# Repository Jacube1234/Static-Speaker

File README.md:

# Static-Speaker

<br>
View PCB on KiCanvas

This is my custom radio combined with a speaker designed for the YSWS Static
I chose this project to upgrade the standard kit by integrating an M18 Bluetooth module alongside the original RDA5807 FM radio chip, transforming it into a permanent Bluetooth speaker for my bedroom while keeping the physical over-the-air FM radio chip!

## Features:
- Bluetooth audio streaming directly from a phone
- Over-the-air local FM Radio playback
- One physical push-button to switch modes
- Dual analog potentiometers for volume control

## CAD Model:

## PCB

Schematic

Layout

PCB

## Firmware Overview
Runs on CircuitPython using an RDA5807 library wrapper. A `code.py` script handles I2C tuning for the FM radio, manages the M18 module's mute line via pin A3 (`BT_MUTE`), and toggles between Bluetooth and FM sources using a push button (`SW1`).

## File structure

There's 3 main folders: Firmware, PCB, and Production. The PCB folder contains .kicad_pcb, .kicad_pro, and .kicad_sch. The Firmware folder contains files for the Seeed Xiao code. The production folder will have files for the PCB printing.

## BOM (Bill of Materials):
Here should be everything you need to make this speaker
Most things should be what static sends you except the bluetooth module.

- 1x Seeed Studio XIAO RP2040
- 1x MH-M18 Bluetooth Audio Module
- 1x RDA5807FP FM Radio Tuner Chip
- 1x TDA2822 Audio Amplifier Chip
- 1x WH148 10kΩ Potentiometer
- 4x 1kΩ Resistors 
- 1x 3.5mm Jack (for FM Radio Antenna)
- 2x 10uF Capacitors
- 2x 100uF Capacitors
- 2x 30mm Speakers
- 1x 12mm Momentary Push Button Mode switch
- Hookup wire (for off-board connections)
- 1x Custom PCB

## Software

- Kicad recommended to view the Gerber files or the general `.pcb` `.pro` `.sch` files
- Thonny or VSCode for programming the board.

## Tools:

- Soldering Iron
- Solder

## How to build/replicate
1. **Gather Parts:** Get **everything** that is on the BOM.
2. **Solder the PCB:** Solder all components onto your custom PCB using a soldering iron.
3. **Print & Mount Case:** 3D print your enclosure design, then mechanically secure and screw the potentiometers (`RV1`/`RV2`) and push button (`SW1`) into place.
4. **Wire Peripherals:** Wire your speakers to `J1` and `J2`, and plug a cable into the 3.5mm jack (`CN1`) to serve as the FM antenna.
5. **Flash Firmware:** Install **CircuitPython** onto your Seeed XIAO RP2040.
6. **Add Code Files:** Copy the `RDA5807.py` library and your `code.py` script directly onto the board's `CIRCUITPY` drive.
7. **Power Up & Test:** Connect USB power (+5V). Pair your phone via Bluetooth to the M18 module or press the push button (`SW1`) to switch over to FM radio mode.
8. **Enjoy:** Adjust your volume knobs and enjoy your custom speaker!

## Extra stuff
In Hackpad style -
Hi guys

Bye guys

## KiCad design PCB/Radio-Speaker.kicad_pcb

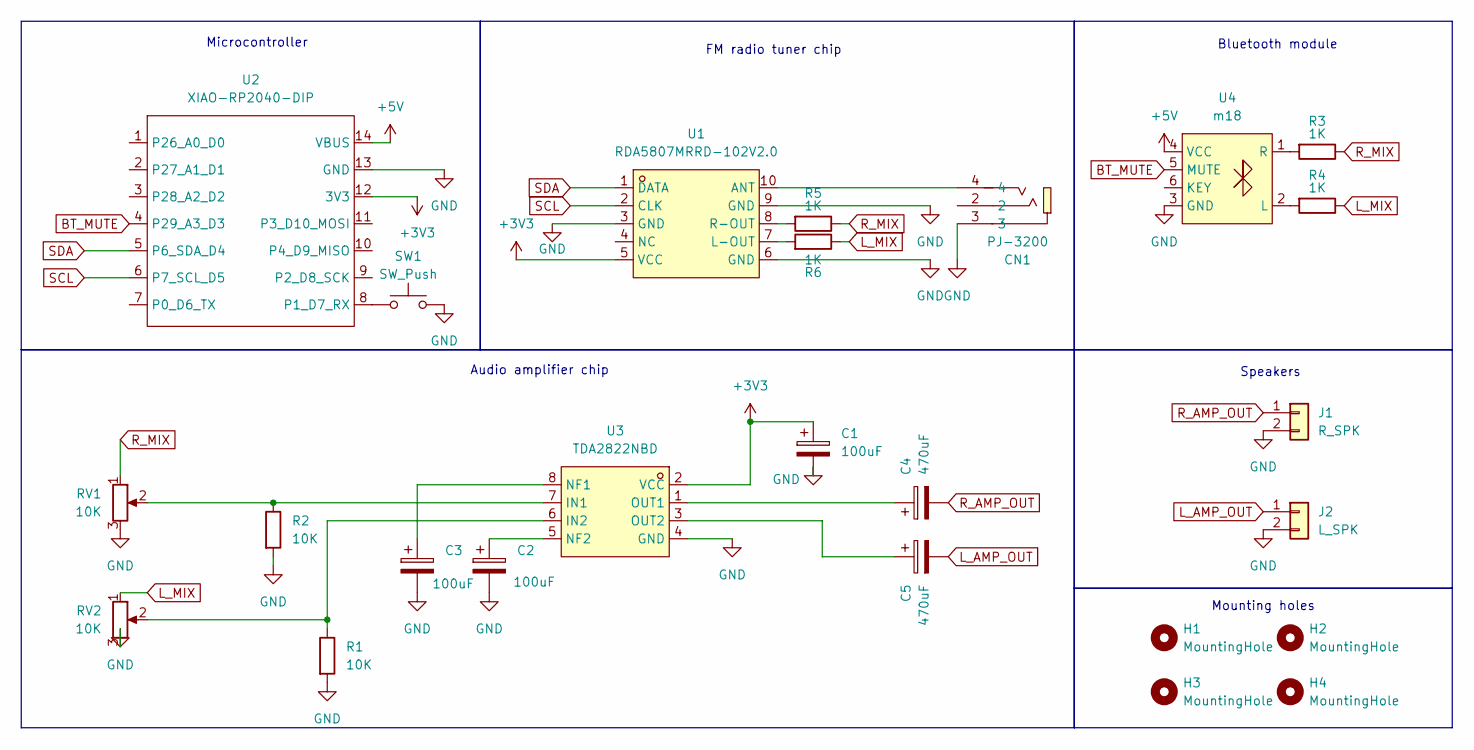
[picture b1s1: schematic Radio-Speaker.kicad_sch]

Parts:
C1, C2, C3: 100uF; CP_Radial_D6.3mm_P2.50mm
C4, C5: 470uF; CP_Radial_D6.3mm_P2.50mm
CN1: PJ-3200; AUDIO-TH_PJ-3200; MPN PJ-3200; LCSC Part C2689690
H1, H2, H3, H4: MountingHole; MountingHole_2.5mm
J1: R_SPK; PinHeader_1x02_P2.54mm_Vertical
J2: L_SPK; PinHeader_1x02_P2.54mm_Vertical
R1, R2: 10K; R_Axial_DIN0207_L6.3mm_D2.5mm_P7.62mm_Horizontal
R3, R4, R5, R6: 1K; R_Axial_DIN0207_L6.3mm_D2.5mm_P7.62mm_Horizontal
RV1, RV2: 10K; PinHeader_1x03_P2.54mm_Vertical
SW1: SW_Push; PinHeader_1x02_P2.54mm_Vertical
U1: RDA5807MRRD-102V2.0; RDA5807; MPN RDA5807MRRD-102V2.0; LCSC Part C9900205627
U2: XIAO-RP2040-DIP
U3: TDA2822NBD; DIP-8_W7.62mm; MPN TDA2822NBD; LCSC Part C51927337
U4: m18

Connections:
+3V3: C1.1, U1.5 (VCC), U2.12 (3V3), U3.2 (VCC)
+5V: U2.14 (VBUS), U4.4 (VCC)
BT_MUTE: U2.4 (P29_A3_D3), U4.5 (MUTE)
GND: C1.2, C2.2, C3.2, CN1.3, J1.2, J2.2, R1.2, R2.2, RV1.3, RV2.3, SW1.2, U1.3 (GND), U1.6 (GND), U1.9 (GND), U2.13 (GND), U3.4 (GND), U4.3 (GND)
L_AMP_OUT: C5.2, J2.1
L_MIX: R4.1, R6.1, RV2.1
unnamed: CN1.4, U1.10 (ANT)
unnamed: R6.2, U1.7 (L-OUT)
unnamed: R5.2, U1.8 (R-OUT)
unnamed: SW1.1, U2.8 (P1_D7_RX)
unnamed: R2.1, RV1.2, U3.7 (IN1)
unnamed: R1.1, RV2.2, U3.6 (IN2)
unnamed: C3.1, U3.8 (NF1)
unnamed: C2.1, U3.5 (NF2)
unnamed: C4.1, U3.1 (OUT1)
unnamed: C5.1, U3.3 (OUT2)
unnamed: R4.2, U4.2 (L)
unnamed: R3.2, U4.1 (R)
R_AMP_OUT: C4.2, J1.1
R_MIX: R3.1, R5.1, RV1.1
SCL: U1.2 (CLK), U2.6 (P7_SCL_D5)
SDA: U1.1 (DATA), U2.5 (P6_SDA_D4)

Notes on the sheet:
Audio amplifier chip
Mounting holes
Bluetooth module
Speakers
FM radio tuner chip
Microcontroller

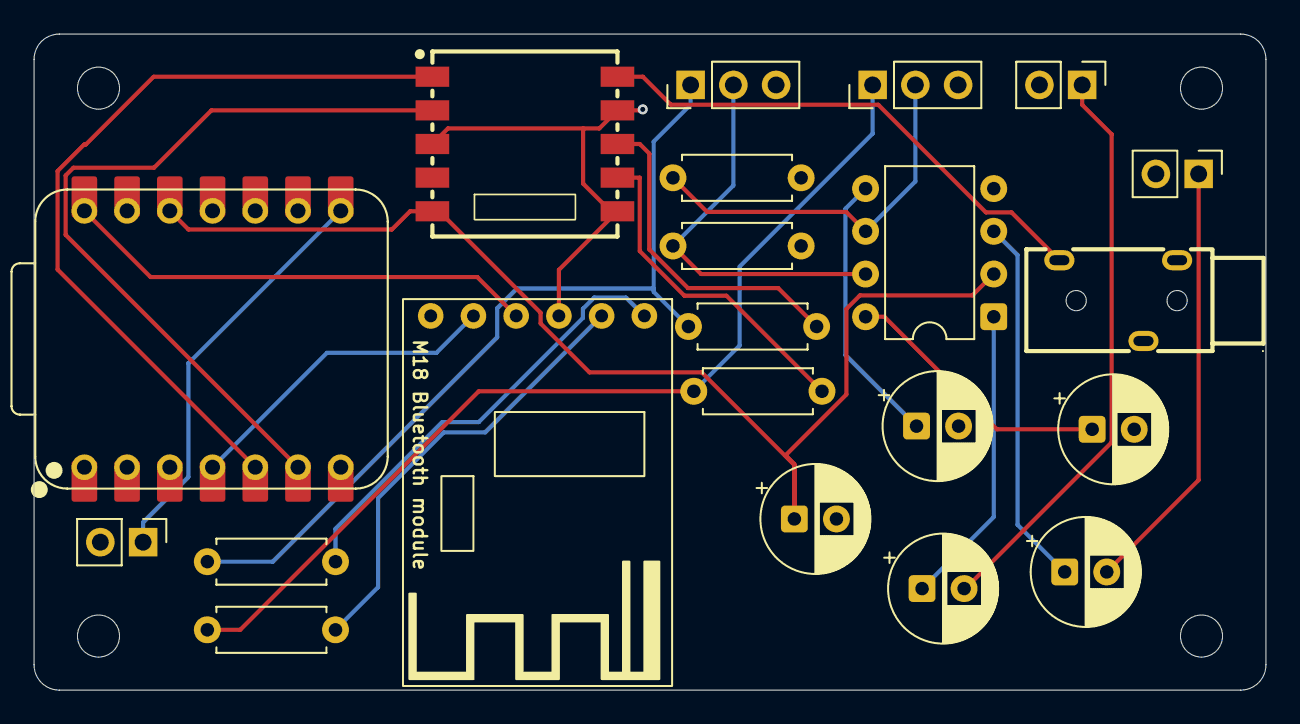
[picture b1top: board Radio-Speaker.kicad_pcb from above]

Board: 2 copper layers, 73.2 x 39.0 mm, 25 parts (0 on the bottom side), 22 nets.

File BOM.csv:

"Reference","Qty","Value","DNP","Exclude from BOM","Exclude from Board","Footprint","Datasheet"
"C1,C2,C3","3","100uF","","","","Capacitor_THT:CP_Radial_D6.3mm_P2.50mm",""
"C4,C5","2","470uF","","","","Capacitor_THT:CP_Radial_D6.3mm_P2.50mm",""
"CN1","1","PJ-3200","","","","Static:AUDIO-TH_PJ-3200","https://www.lcsc.com/datasheet/C2689690.pdf"
"J1","1","R_SPK","","","","Connector_PinHeader_2.54mm:PinHeader_1x02_P2.54mm_Vertical",""
"J2","1","L_SPK","","","","Connector_PinHeader_2.54mm:PinHeader_1x02_P2.54mm_Vertical",""
"R1,R2","2","10K","","","","Resistor_THT:R_Axial_DIN0207_L6.3mm_D2.5mm_P7.62mm_Horizontal",""
"R3,R4,R5,R6","4","1K","","","","Resistor_THT:R_Axial_DIN0207_L6.3mm_D2.5mm_P7.62mm_Horizontal",""
"RV1,RV2","2","10K","","","","Connector_PinHeader_2.54mm:PinHeader_1x03_P2.54mm_Vertical",""
"SW1","1","SW_Push","","","","Connector_PinHeader_2.54mm:PinHeader_1x02_P2.54mm_Vertical",""
"U1","1","RDA5807MRRD-102V2.0","","","","Static:RDA5807","https://www.lcsc.com/datasheet/C9900205627.pdf"
"U2","1","XIAO-RP2040-DIP","","","","Static:XIAO-RP2040-DIP",""
"U3","1","TDA2822NBD","","","","Package_DIP:DIP-8_W7.62mm","https://www.lcsc.com/datasheet/C51927337.pdf"
"U4","1","m18","","","","Static:m18","https://www.sunrom.com/download/705.pdf"
